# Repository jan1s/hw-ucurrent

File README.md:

# uCurrent Clone

This is a copy of the famous µCurrent of Dave Jones from EEVBlog.
Have a look at the [original project site](http://www.eevblog.com/projects/ucurrent/).

## Hardware

Project schematic.

Project board render.

## BOM
| Identifier | Type/Value | Quantity | Supplier Id | Supplier | Comment |
| ---        | ---        | ---      | ---         | ---      | ---     |
| R1 | 0.01 Ω 0.5% | 1 | 603-RL1206FR070R01L | [Mouser][mouser] |
| R8 | 10 Ω 0.1% | 1 | 279-RP73D2A10RBTG | [Mouser][mouser] |
| R9, R10, R12 | 100 Ω 1% | 3 | SMD-0603 100 | [Reichelt][reichelt] |
| R4 | 470 Ω | 1 | SMD-0603 470 | [Reichelt][reichelt] |
| R5 | 1 kΩ 0.1% | 1 | SPR-0603 1,00K | [Reichelt][reichelt] |
| R2 | 10 kΩ 0.1% | 1 | SPR-0603 10,0K | [Reichelt][reichelt] |
| R11 | 24 kΩ 0.1% | 1 | SPR-0603 24,0K | [Reichelt][reichelt] |
| R3 | 75 kΩ 0.1% | 1 | SPR-0603 75,0K | [Reichelt][reichelt] |
| R6, R7 | 100 kΩ 1% | 2 | SMD-0603 100K | [Reichelt][reichelt] |
| C3, C8, C13, C14 | 100 nF | 4 | X7R-G0603 100N | [Reichelt][reichelt] |
| LED1 | LED green | 1 | LG L29K | [Reichelt][reichelt] |
| J1 | Banana Jack | 1 | PK 4 SW | [Reichelt][reichelt] |
| J2 | Banana Jack | 1 | PK 4 RT | [Reichelt][reichelt] |
| J3 | Banana Jack | 1 | BB 4 SW | [Reichelt][reichelt] |
| J4 | Banana Jack | 1 | BB 4 RT | [Reichelt][reichelt] |
| BAT | Batteryholder | 1 | KZH 20SMD-2 | [Mouser][mouser] |
| SW1, SW2 | Switch | 2 | Switches Micro SMD | [Aliexpress][aliexpress] |
| U1 | MAX4239ASA | 1 | 700-MAX4239ASA | [Mouser][mouser] |
| U2 | LMV321M5X | 1 | 926-LMV321M5X/NOPB | [Mouser][mouser] |
| U3 | TPS3809L30DBVR | 1 | 595-TPS3809L30DBVTG4 | [Mouser][mouser] |

[reichelt]: http://www.reichelt.de
[mouser]: http://mouser.com
[aliexpress]: http://www.aliexpress.com

## license

This work is licensed under a [Creative Commons Attribution-ShareAlike 3.0 Unported License](http://creativecommons.org/licenses/by-sa/3.0/).

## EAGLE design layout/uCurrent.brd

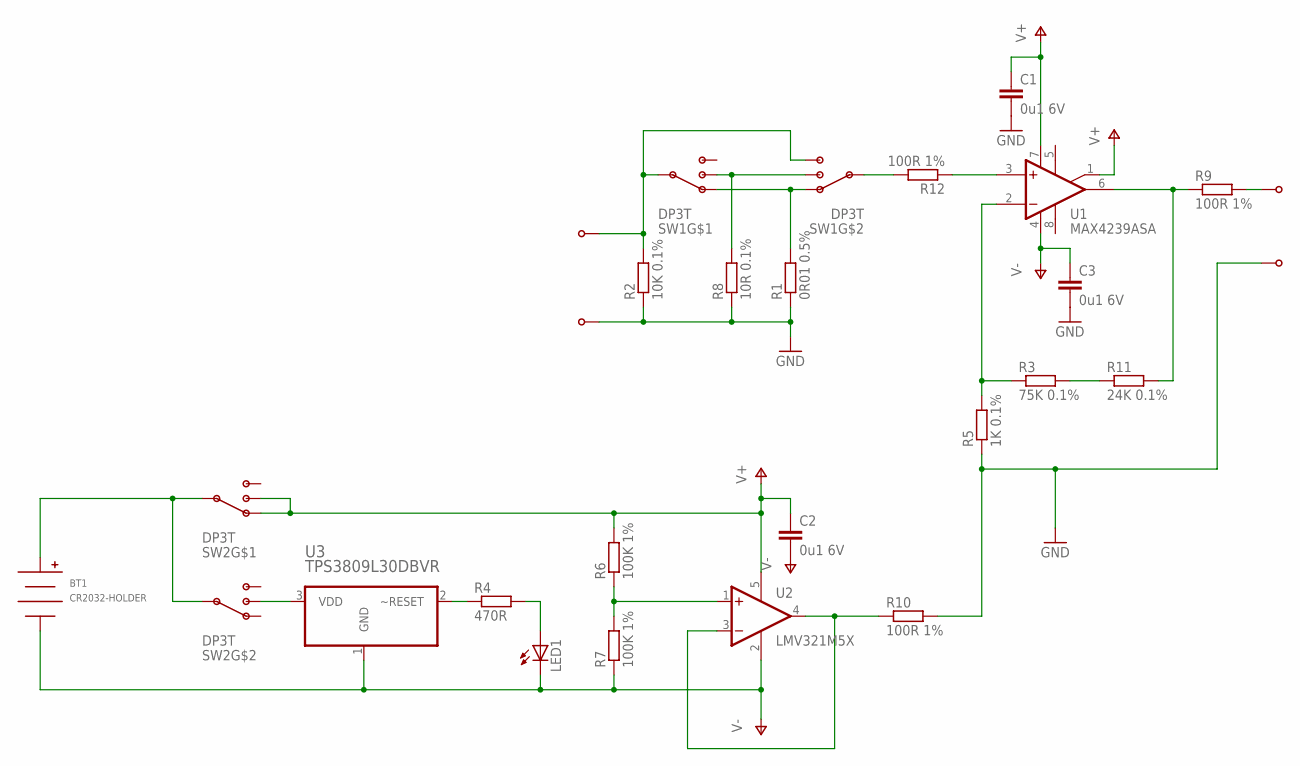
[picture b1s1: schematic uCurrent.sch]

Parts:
BT1: CR2032-HOLDER; CH28-2032LF
C1, C2, C3: 0u1 6V; C0805
LED1: LEDCHIPLED_0805; CHIPLED_0805
R1: 0R01 0.5%; R1206
R2: 10K 0.1%; R0805
R3: 75K 0.1%; R0805
R4: 470R; R0805
R5: 1K 0.1%; R0805
R6, R7: 100K 1%; R0805
R8: 10R 0.1%; R0805
R9, R10, R12: 100R 1%; R0805
R11: 24K 0.1%; R0805
SW1, SW2: DP3T
U1: MAX4239ASA; SO08
U2: LMV321M5X; SOT23-5
U3: TPS3809L30DBVR; SOT95P280X145-3N
U$2, U$3, U$4, U$5: BANANA-JACK; BANANA-PRINT

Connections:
GND: C1.2, C3.2, R1.1, R2.1, R5.1, R8.1, R10.2, U$3.P$1, U$5.P$1
unnamed: R10.1, U2.3 (-IN), U2.4 (OUT)
unnamed: R2.2, SW1.P$4 (1), SW1.P$C1 (C), U$2.P$1
unnamed: R8.2, SW1.P$2 (2), SW1.P$5 (2)
unnamed: R1.2, SW1.P$3 (3), SW1.P$6 (3)
unnamed: R3.2, R11.1
unnamed: R3.1, R5.2, U1.2 (-IN)
unnamed: R12.2, SW1.P$C2 (C)
unnamed: R9.1, R11.2, U1.6 (OUT)
unnamed: R12.1, U1.3 (+IN)
unnamed: R6.1, R7.2, U2.1 (+IN)
unnamed: R4.1, U3.2 (~RESET)
unnamed: LED1.A, R4.2
unnamed: SW2.P$5 (2), U3.3 (VDD)
unnamed: BT1.POS, SW2.P$C1 (C), SW2.P$C2 (C)
unnamed: R9.2, U$4.P$1
V+: C1.1, C2.1, R6.2, SW2.P$2 (2), SW2.P$3 (3), U1.1 (NC), U1.7 (V+), U2.5 (V+)
V-: BT1.NEG, C2.2, C3.1, LED1.C, R7.1, U1.4 (V-), U2.2 (V-), U3.1 (GND)

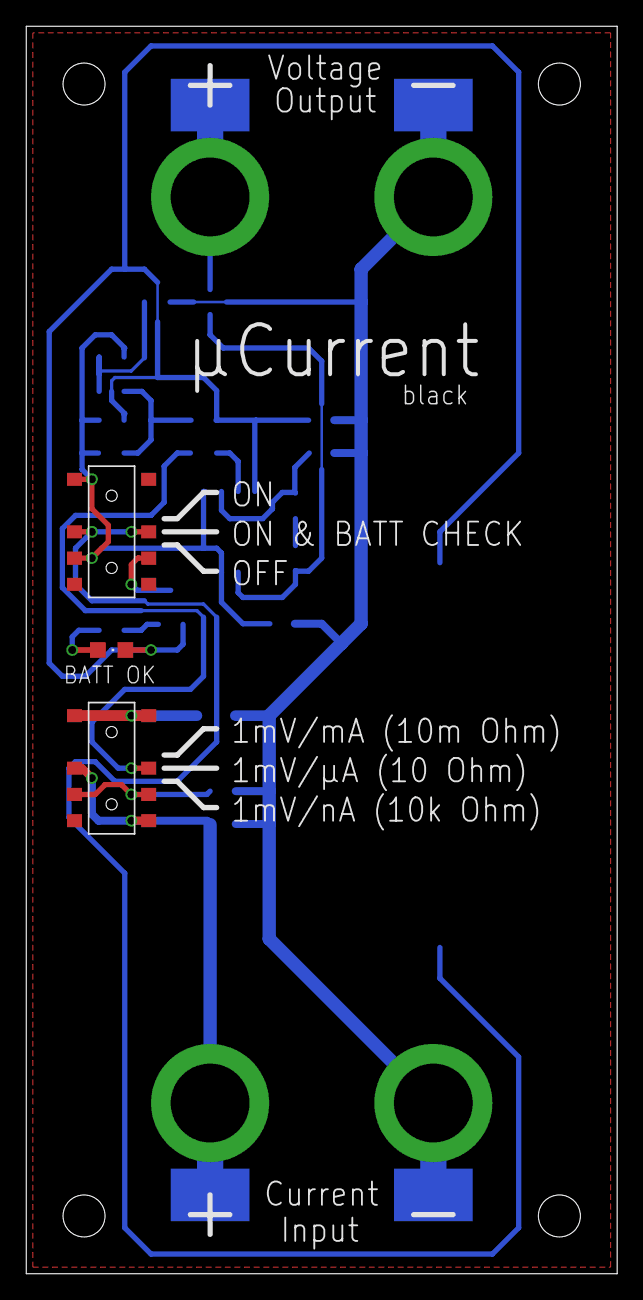
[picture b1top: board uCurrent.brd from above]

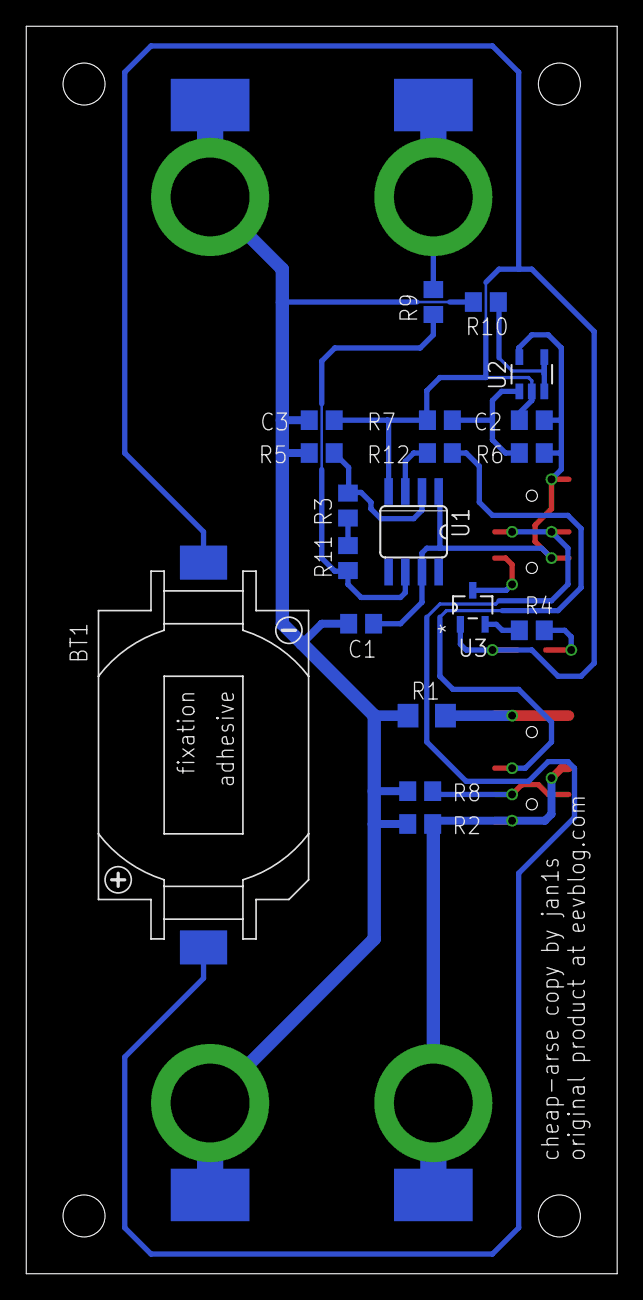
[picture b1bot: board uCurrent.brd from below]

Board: 2 copper layers, 45.0 x 95.0 mm, 26 parts (23 on the bottom side), 18 nets.

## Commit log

2013-06-22 readme
2013-06-29 Forgot first Pin on OpAmp
2013-07-03 Fixed solderstop on banana jack
2014-04-15 Updated Readme with BOM
2014-04-15 Added Banana Plugs to BOM
2014-09-04 Added docu pictures
